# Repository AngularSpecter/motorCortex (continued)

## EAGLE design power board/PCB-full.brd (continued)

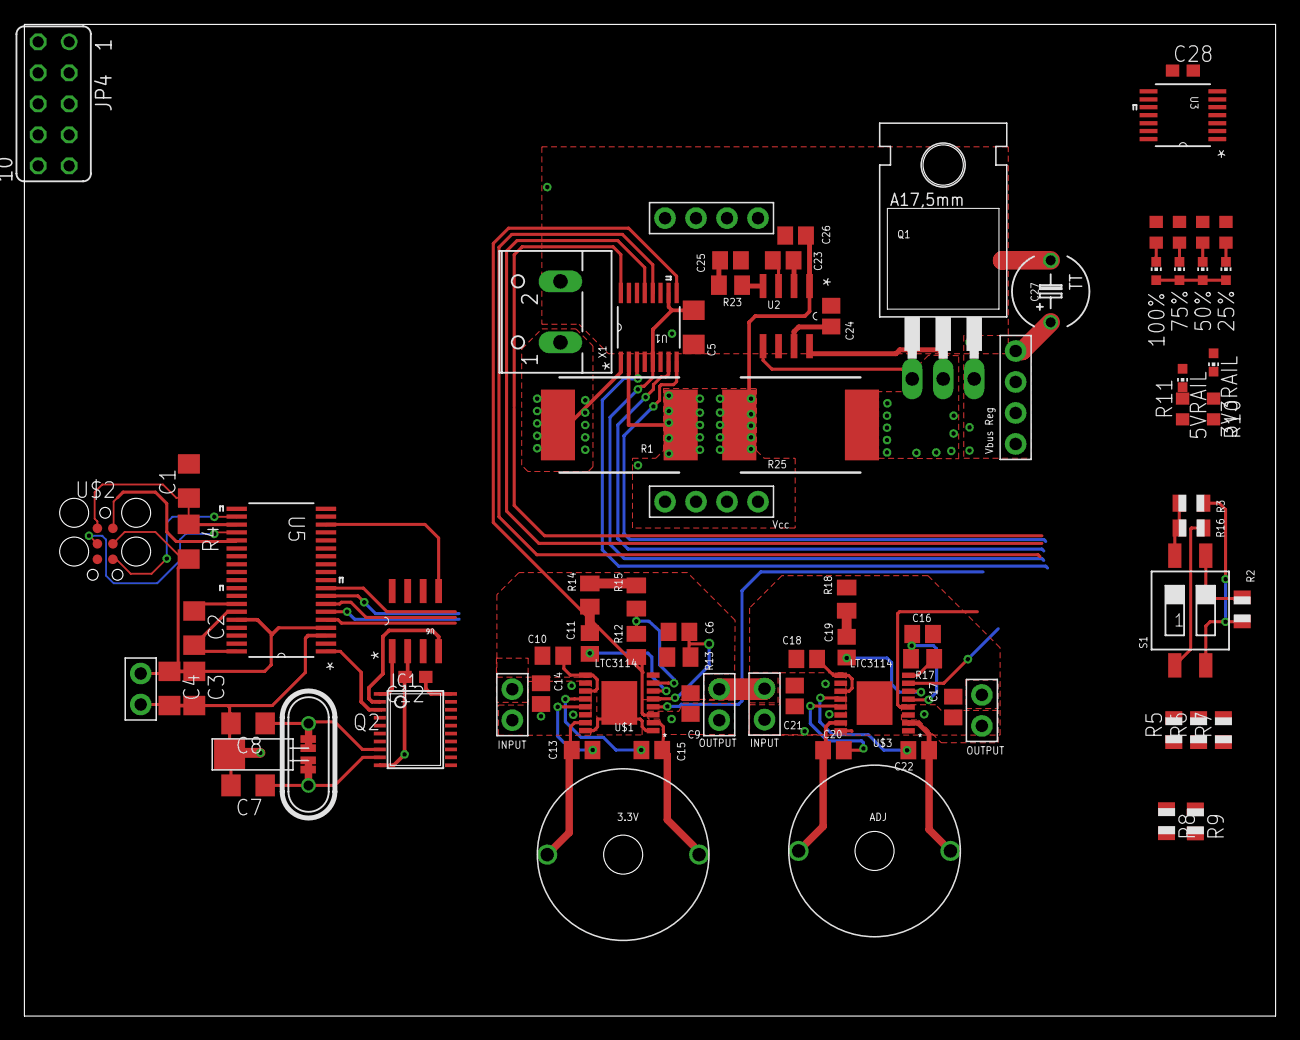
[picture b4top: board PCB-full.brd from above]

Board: 2 copper layers, 102.5 x 81.3 mm, 82 parts (0 on the bottom side), 81 nets.

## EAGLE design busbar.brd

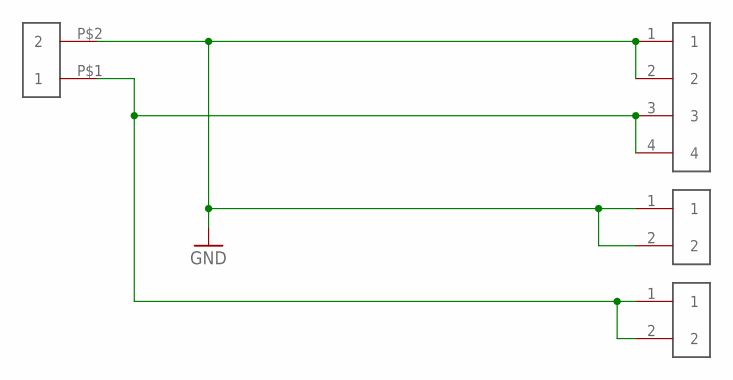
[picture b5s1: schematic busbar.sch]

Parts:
U$1: MOLEX-0436500200; MOLEX_MICROFIT-2
U$2: 1X4_HEADER; 1X4-.1HEADER
U$3, U$4: 1X2_HEADER; 1X2-.1HEADER

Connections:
GND: U$1.P$2 (2), U$2.1, U$2.2, U$3.1, U$3.2
VBUS: U$1.P$1 (1), U$2.3, U$2.4, U$4.1, U$4.2

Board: 2 copper layers, 4 parts (0 on the bottom side), 2 nets, no tracks yet.

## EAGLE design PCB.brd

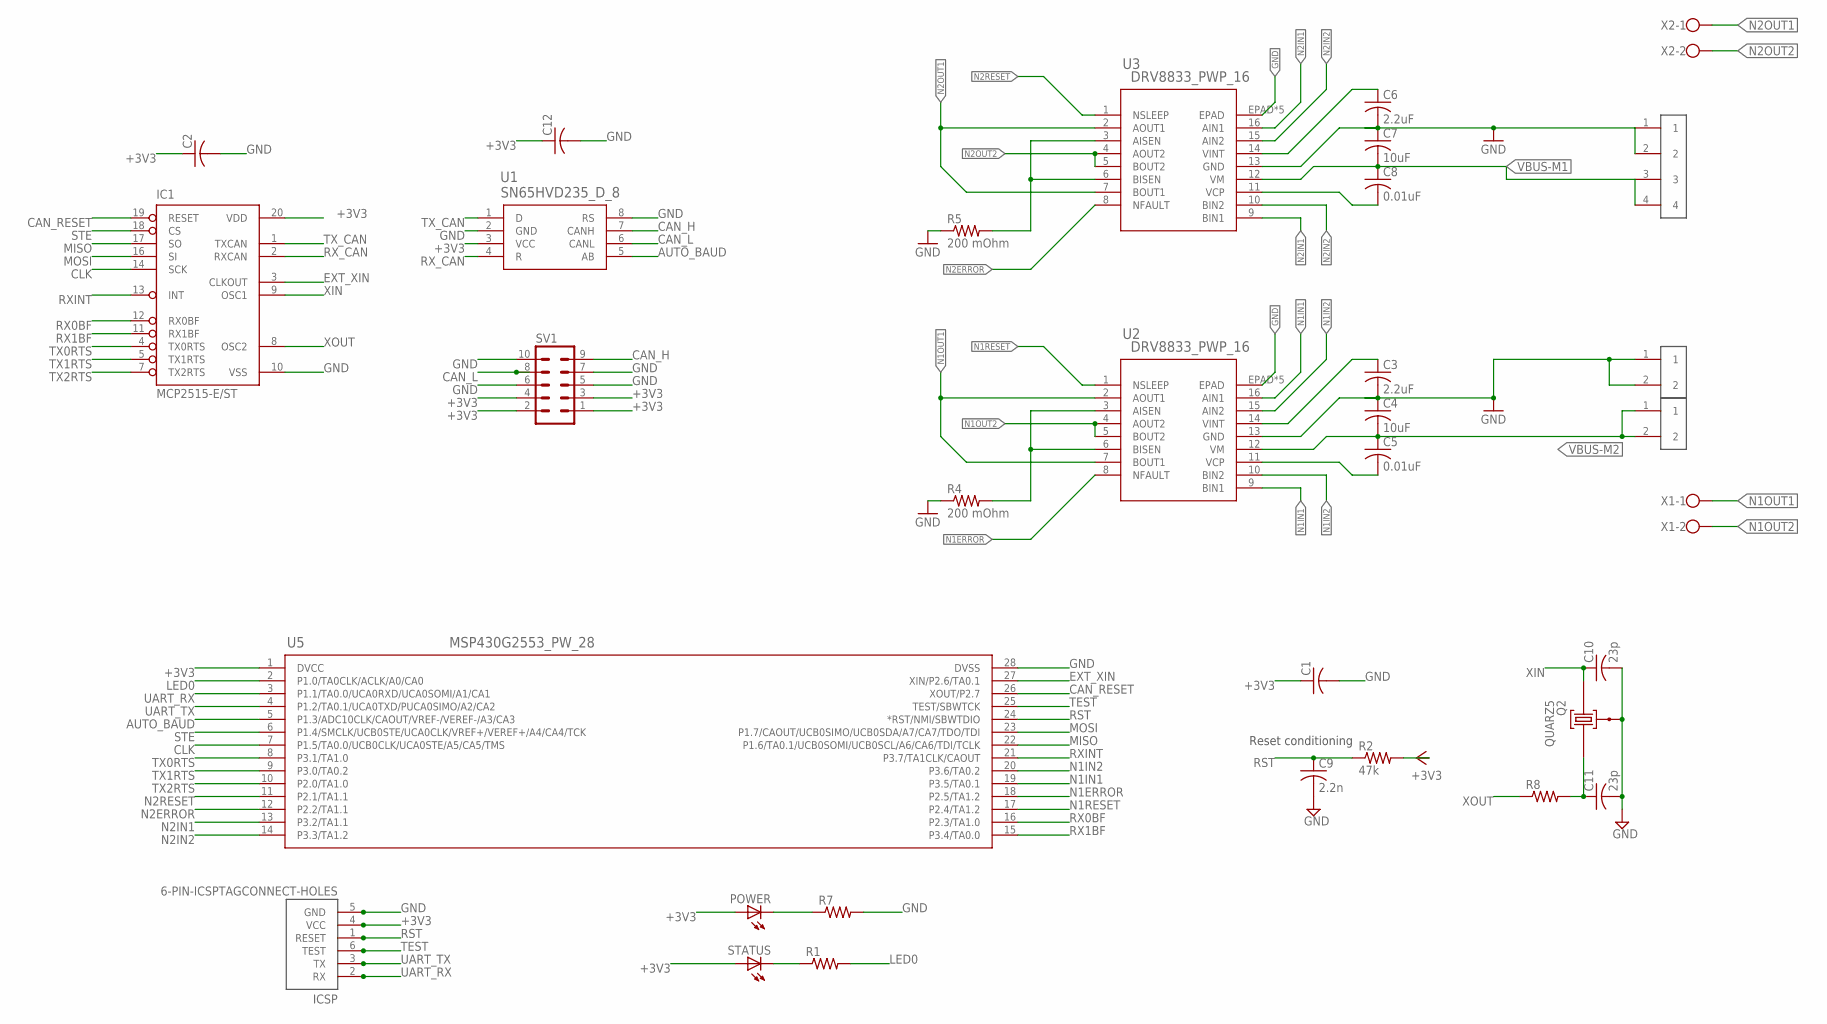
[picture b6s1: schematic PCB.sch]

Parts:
C1, C2, C12: C-USC0603; C0603
C3, C6: 2.2uF; C1206
C4, C7: 10uF; C1206
C5, C8: 0.01uF; C1206
C9: 2.2n; C0603
C10, C11: 23p; C1206
IC1: MCP2515-E/ST; TSSOP20
ICSP: 6-PIN-ICSPTAGCONNECT-HOLES; TAGCONNECT-HOLES
POWER: LEDCHIP-LED0603; CHIP-LED0603
Q2: QUARZ5
R1, R7, R8: R-US_R0603; R0603
R2: 47k; R0603
R4, R5: 200 mOhm; R0805
STATUS: LEDCHIP-LED0603; CHIP-LED0603
SV1: MA05-2
U1: SN65HVD235_D_8; D8
U2, U3: DRV8833_PWP_16; PWP16_2P31X2P46
U5: MSP430G2553_PW_28; PW28
U$2: 1X4_HEADER; 1X4-.1HEADER
U$3, U$4: 1X2_HEADER; 1X2-.1HEADER
X1, X2: W237-102

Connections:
+3V3: C1.1, C2.1, C12.1, IC1.20 (VDD), ICSP.4 (VCC), POWER.A, R2.2, STATUS.A, SV1.1, SV1.2, SV1.3, SV1.4, U1.3 (VCC), U5.1 (DVCC)
AUTO_BAUD: U1.5 (AB), U5.5 (P1.3/ADC10CLK/CAOUT/VREF-/VEREF-/A3/CA3)
CAN_H: SV1.9, U1.7 (CANH)
CAN_L: SV1.8, U1.6 (CANL)
CAN_RESET: IC1.19 (RESET), U5.26 (XOUT/P2.7)
CLK: IC1.14 (SCK), U5.7 (P1.5/TA0.0/UCB0CLK/UCA0STE/A5/CA5/TMS)
EXT_XIN: IC1.3 (CLKOUT), U5.27 (XIN/P2.6/TA0.1)
GND: C1.2, C2.2, C3.2, C4.1, C6.2, C7.1, C9.2, C10.2, C11.2, C12.2, IC1.10 (VSS), ICSP.5 (GND), Q2.GND@0 (0), R4.1, R5.1, R7.2, SV1.5, SV1.6, SV1.7, SV1.10, U1.2 (GND), U1.8 (RS), U2.13 (GND), U2.EPAD, U2.V (EPAD), U2.V_2 (EPAD), U2.V_3 (EPAD), U2.V_6 (EPAD), U3.13 (GND), U3.EPAD, U3.V (EPAD), U3.V_2 (EPAD), U3.V_3 (EPAD), U3.V_6 (EPAD), U5.28 (DVSS), U$2.1, U$2.2, U$3.1, U$3.2
LED0: R1.2, U5.2 (P1.0/TA0CLK/ACLK/A0/CA0)
MISO: IC1.17 (SO), U5.22 (P1.6/TA0.1/UCB0SOMI/UCB0SCL/A6/CA6/TDI/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)
MOSI: IC1.16 (SI), U5.23 (P1.7/CAOUT/UCB0SIMO/UCB0SDA/A7/CA7/TDO/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)
N1ERROR: U2.8 (NFAULT), U5.18 (P2.5/TA1.2)
N1IN1: U2.9 (BIN1), U2.16 (AIN1), U5.19 (P3.5/TA0.1)
N1IN2: U2.10 (BIN2), U2.15 (AIN2), U5.20 (P3.6/TA0.2)
N1OUT1: U2.2 (AOUT1), U2.7 (BOUT1), X1.1
N1OUT2: U2.4 (AOUT2), U2.5 (BOUT2), X1.2
N1RESET: U2.1 (NSLEEP), U5.17 (P2.4/TA1.2)
N1SENSE: R4.2, U2.3 (AISEN), U2.6 (BISEN)
N1SENSE1: R5.2, U3.3 (AISEN), U3.6 (BISEN)
N1VINT: C3.1, U2.14 (VINT)
N2ERROR: U3.8 (NFAULT), U5.12 (P2.2/TA1.1)
N2IN1: U3.9 (BIN1), U3.16 (AIN1), U5.13 (P3.2/TA1.1)
N2IN2: U3.10 (BIN2), U3.15 (AIN2), U5.14 (P3.3/TA1.2)
N2OUT1: U3.2 (AOUT1), U3.7 (BOUT1), X2.1
N2OUT2: U3.4 (AOUT2), U3.5 (BOUT2), X2.2
N2RESET: U3.1 (NSLEEP), U5.11 (P2.1/TA1.1)
N2VCP: C8.2, U3.11 (VCP)
N2VINT: C6.1, U3.14 (VINT)
unnamed: R1.1, STATUS.C
unnamed: C5.2, U2.11 (VCP)
unnamed: POWER.C, R7.1
RST: C9.1, ICSP.1 (RESET), R2.1, U5.24 (*RST/NMI/SBWTDIO)
RX0BF: IC1.12 (RX0BF), U5.16 (P2.3/TA1.0)
RX1BF: IC1.11 (RX1BF), U5.15 (P3.4/TA0.0)
RXINT: IC1.13 (INT), U5.21 (P3.7/TA1CLK/CAOUT)
RX_CAN: IC1.2 (RXCAN), U1.4 (R)
STE: IC1.18 (CS), U5.6 (P1.4/SMCLK/UCB0STE/UCA0CLK/VREF+/VEREF+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)
TEST: ICSP.6 (TEST), U5.25 (TEST/SBWTCK)
TX0RTS: IC1.4 (TX0RTS), U5.8 (P3.1/TA1.0)
TX1RTS: IC1.5 (TX1RTS), U5.9 (P3.0/TA0.2)
TX2RTS: IC1.7 (TX2RTS), U5.10 (P2.0/TA1.0)
TX_CAN: IC1.1 (TXCAN), U1.1 (D)
UART_RX: ICSP.2 (RX), U5.3 (P1.1/TA0.0/UCA0RXD/UCA0SOMI/A1/CA1)
UART_TX: ICSP.3 (TX), U5.4 (P1.2/TA0.1/UCA0TXD/PUCA0SIMO/A2/CA2)
VBUS-M1: C7.2, C8.1, U3.12 (VM), U$2.3, U$2.4
VBUS-M2: C4.2, C5.1, U2.12 (VM), U$4.1, U$4.2
XIN: C10.1, IC1.9 (OSC1), Q2.2
XOUT: IC1.8 (OSC2), R8.1
XOUT_C: C11.1, Q2.1, R8.2

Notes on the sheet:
Reset conditioning

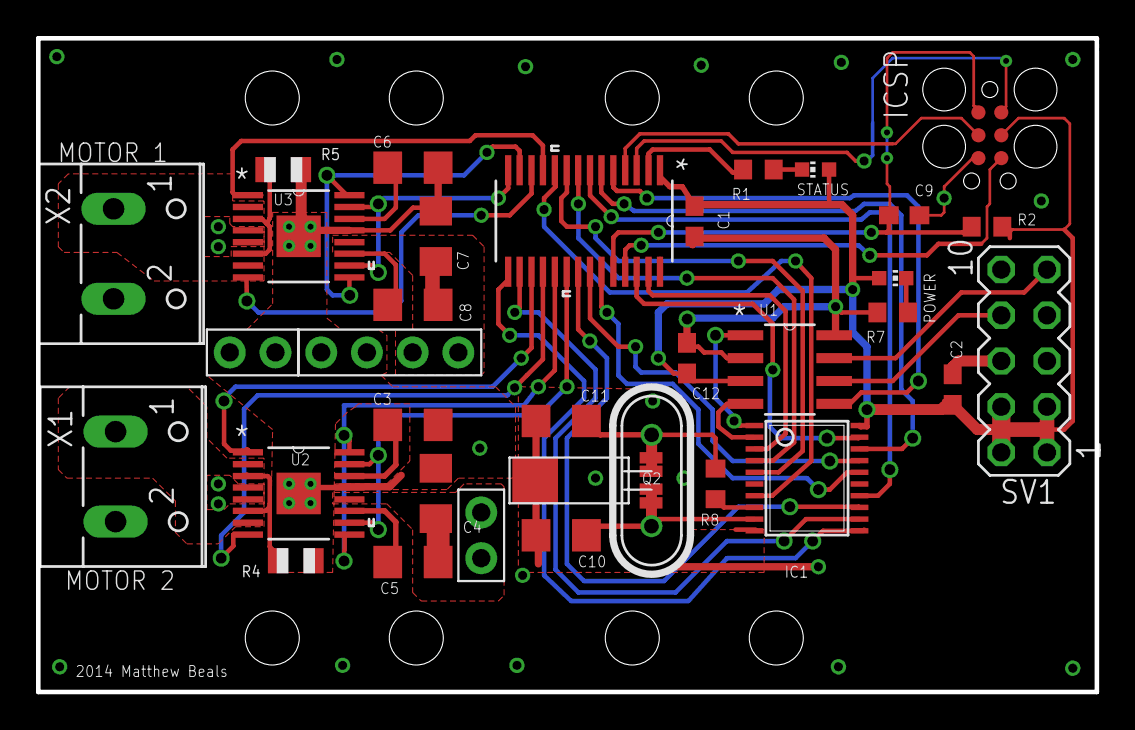
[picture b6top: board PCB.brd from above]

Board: 2 copper layers, 58.8 x 36.3 mm, 33 parts (0 on the bottom side), 49 nets.

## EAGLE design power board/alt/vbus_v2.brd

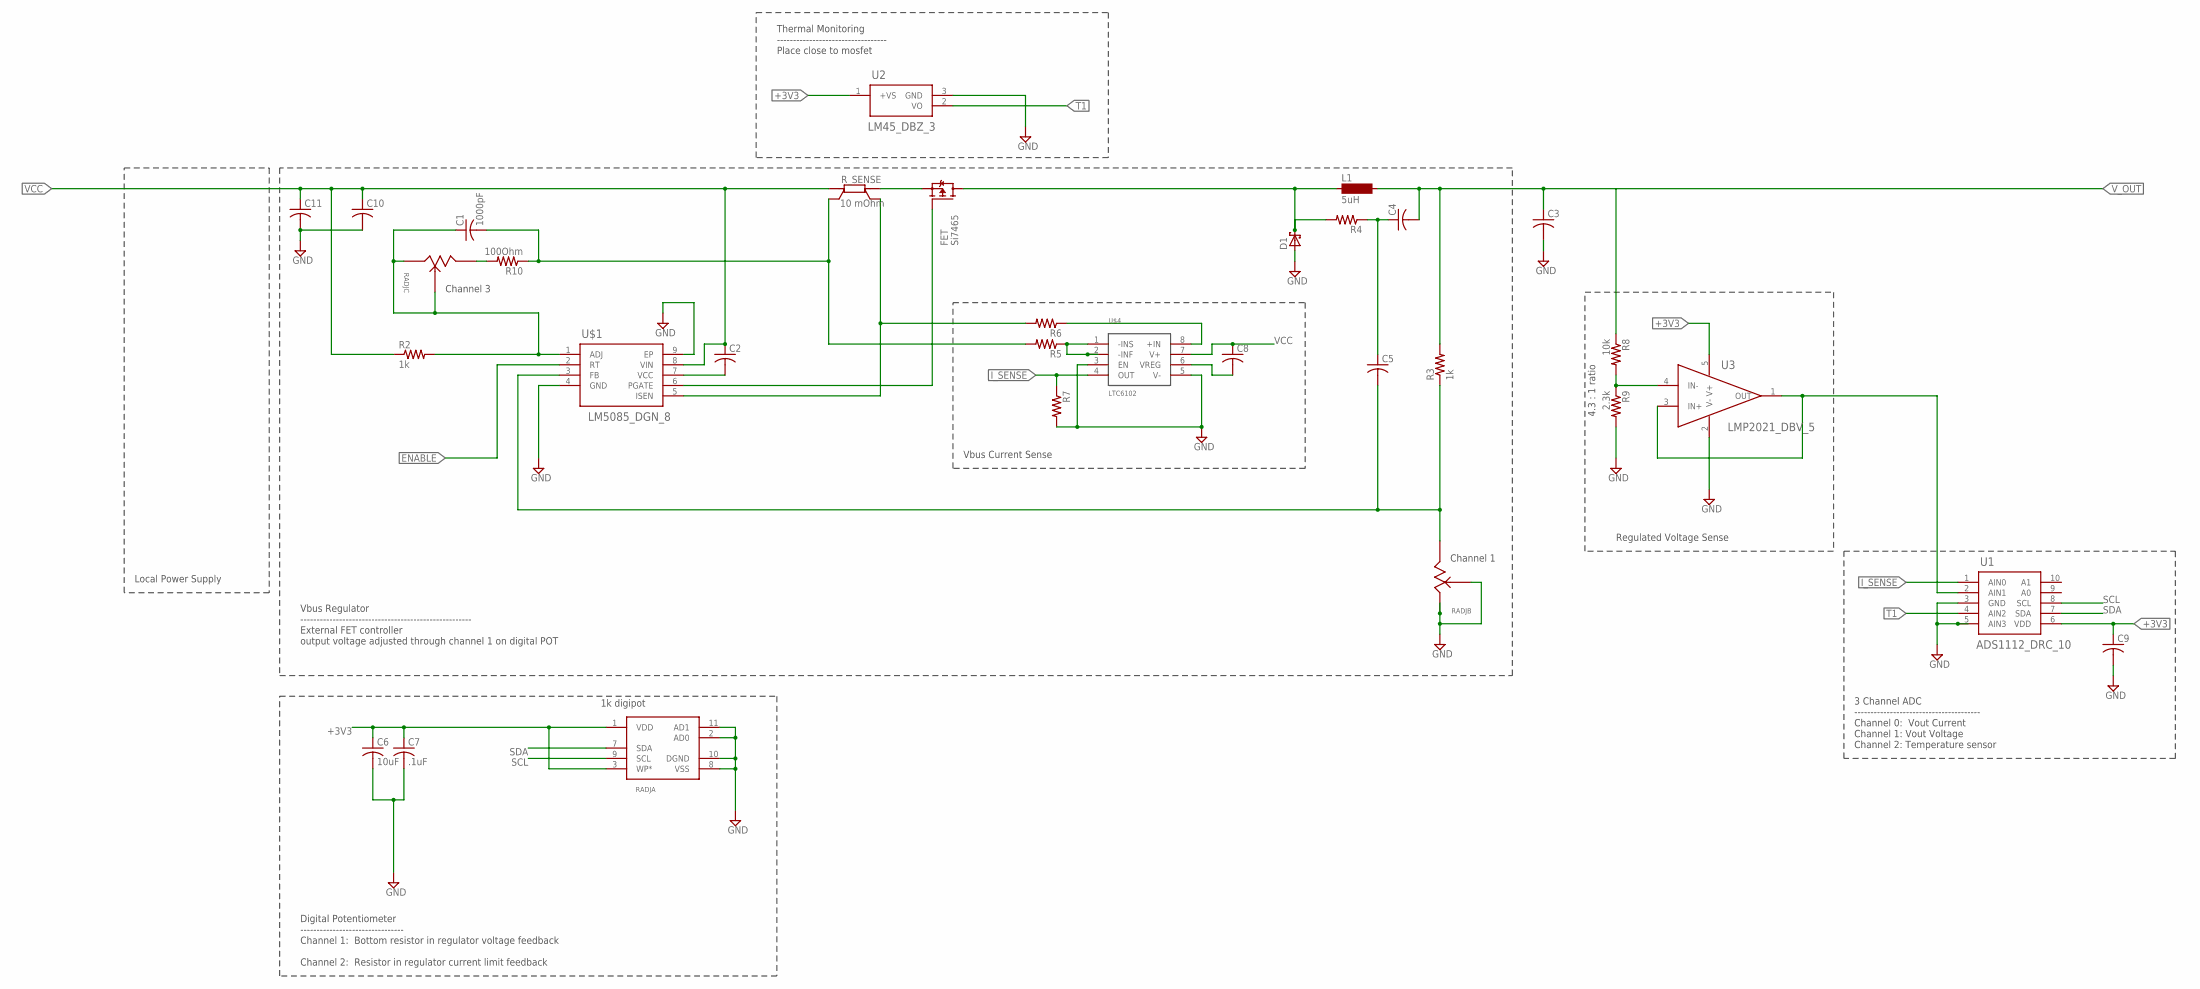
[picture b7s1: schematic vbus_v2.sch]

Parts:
C1: 1000pF; C0805
C2, C3, C4, C5, C8, C9, C10, C11: C-USC0805; C0805
C6: 10uF; C0805
C7: .1uF; C0805
D1: SCHOTTKY-DIODETO92H; TO92H
FET: Si7465; SOT-223
L1: 5uH; MS50
R2, R3: 1k; M0805
R4, R5, R6, R7: R-US_M0805; M0805
R8: 10k; M0805
R9: 2.3k; M0805
R10: 100Ohm; M0805
RADJ: AD5252; RU_14
R_SENSE: 10 mOhm; SMV
U1: ADS1112_DRC_10; DG6-10
U2: LM45_DBZ_3; MF03A
U3: LMP2021_DBV_5; MF05A
U$1: LM5085_DGN_8; MUY08A
U$4: LTC6102; MS8

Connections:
+3V3: C6.1, C7.1, C9.1, RADJ.1 (VDD), RADJ.3 (WP*), U1.6 (VDD), U2.1 (+VS), U3.5 (V+)
ENABLE: U$1.2 (RT)
FB: C5.2, R3.1, RADJ.6 (A1), U$1.3 (FB)
GND: C3.2, C6.2, C7.2, C9.2, C10.2, C11.2, D1.1 (A), R7.2, R9.2, RADJ.2 (AD0), RADJ.4 (W1), RADJ.5 (B1), RADJ.8 (VSS), RADJ.10 (DGND), RADJ.11 (AD1), U1.3 (GND), U1.5 (AIN3), U2.3 (GND), U3.2 (V-), U$1.4 (GND), U$1.9 (EP), U$4.3 (EN), U$4.5 (V-)
I_SENSE: R7.1, U1.1 (AIN0), U$4.4 (OUT)
unnamed: FET.3 (S), R_SENSE.I1 (A)
unnamed: FET.1 (G), U$1.6 (PGATE)
unnamed: R5.1, U$4.1 (-INS), U$4.2 (-INF)
unnamed: R6.1, U$4.8 (+IN)
unnamed: C2.2, U$1.7 (VCC)
unnamed: C8.2, U$4.6 (VREG)
unnamed: D1.2 (C), FET.2 (D), FET.4 (D), L1.1, R4.2
unnamed: R10.2, RADJ.12 (A1)
unnamed: C4.1, C5.1, R4.1
unnamed: U1.2 (AIN1), U3.1 (OUT), U3.3 (IN+)
R_SENSE: C1.1, R2.2, RADJ.13 (B1), RADJ.14 (W1), U$1.1 (ADJ)
SCL: RADJ.9 (SCL), U1.8 (SCL)
SDA: RADJ.7 (SDA), U1.7 (SDA)
T1: U1.4 (AIN2), U2.2 (VO)
VCC: C2.1, C8.1, C10.1, C11.1, R2.1, R_SENSE.I2 (B), U$1.8 (VIN), U$4.7 (V+)
VCC1: R6.2, R_SENSE.U1 (SA), U$1.5 (ISEN)
VCC_SENSE: C1.2, R5.2, R10.1, R_SENSE.U2 (SB)
V_OUT: C3.1, C4.2, L1.2, R3.2, R8.1
V_SENSE: R8.2, R9.1, U3.4 (IN-)

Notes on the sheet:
Thermal Monitoring ---------------------------------- Place close to mosfet
Vbus Regulator ----------------------------------------------------- External FET controller output voltage adjusted through channel 1 on digital POT
Regulated Voltage Sense
Vbus Current Sense
Digital Potentiometer -------------------------------- Channel 1: Bottom resistor in regulator voltage feedback Channel 2: Resistor in regulator current limit feedback
3 Channel ADC --------------------------------------- Channel 0: Vout Current Channel 1: Vout Voltage Channel 2: Temperature sensor
Local Power Supply
1k digipot
Channel 3
Channel 1
4.3 : 1 ratio

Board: 2 copper layers, 30 parts (0 on the bottom side), 23 nets, no tracks yet.

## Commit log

2013-01-18 Initial Commit of EAGLE PCB files
2013-01-29 Updates to rev 1
2013-01-29 clean up
2013-01-29 Added Errata file
2013-01-30 Magor version revision
    Fixed timer pinout problem
    updated silk screen with new logo
    broke out power and data to different headers
    reworked MCU power isolation
2013-02-02 Updated power managment
    Added LDO for mcu power
    Added buffered voltage divider to allow mcu to measure rail voltage
    Repurposed P1.0 to measure rail voltage
2013-02-09 Added V1.1 firmware
2014-05-08 added power board and gitignore
2014-05-08 fixed merge conflicts
2014-05-08 PCB layout of power rails
2014-05-08 additional pcb work
2014-05-30 major topology changes
2014-05-30 clean up schematics
